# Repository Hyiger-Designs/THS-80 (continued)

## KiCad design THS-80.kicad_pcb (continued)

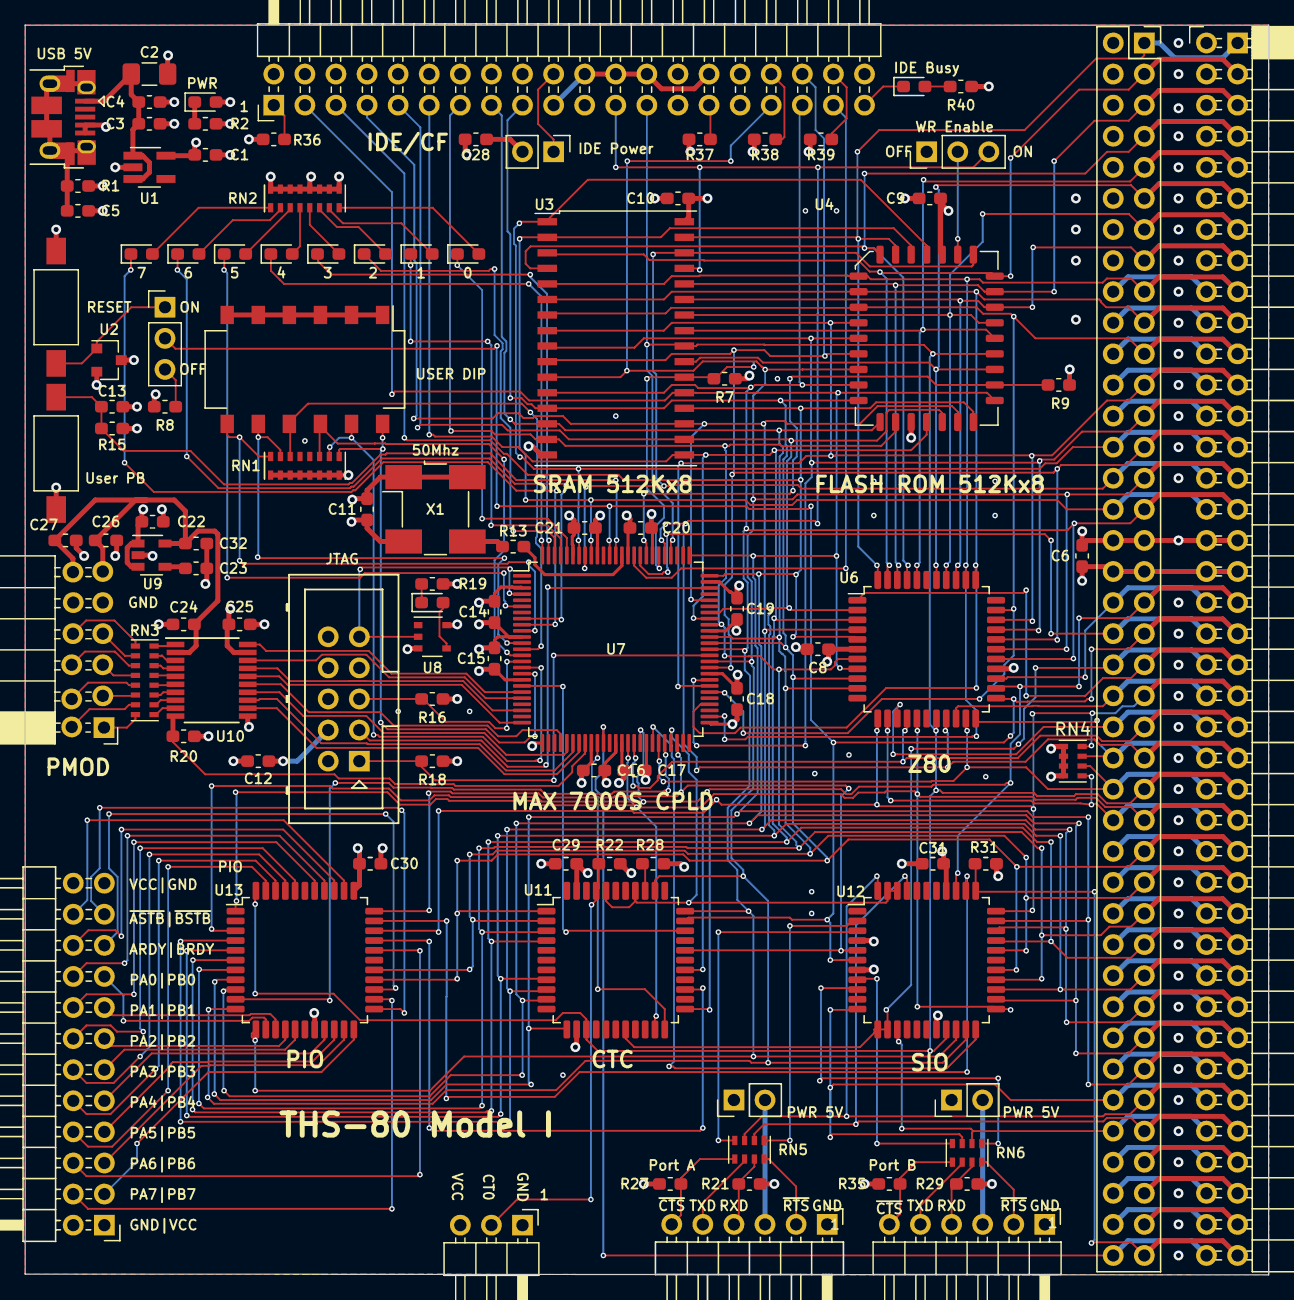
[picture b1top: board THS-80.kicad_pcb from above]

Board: 4 copper layers, 101.6 x 102.1 mm, 102 parts (0 on the bottom side), 188 nets.

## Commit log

2019-08-15 first version
2019-08-15 fixed project library path
2019-08-15 reset annotations, added dip switch
2019-08-15 added switch pullups
2019-08-15 regridded
2019-08-16 connect sheet pins
2019-08-21 connected sheet pins to bus
2019-08-22 Moved CPU, RAM, ROM to sub-sheet
2019-08-22 fixed up interrupt chain wiring
2019-09-02 fixed bus connections
2019-09-03 passed DRC
2019-09-04 started routing
2019-09-05 more routing
2019-09-05 almost there...
2019-09-06 finished routing, passed DRC
2019-09-06 added top/bottom gnd planes and stitching vias
2019-09-06 stitching via tracks added
2019-09-07 pmod changes
2019-09-17 finished routing, drc passed
2019-09-18 track cleanup, fixed slots in ground plane
2019-09-18 more trace cleanup
2019-09-18 fixed gnd plane breaks, adjust silk screens
2019-09-19 more grnd plane fixes
2019-09-19 fixed pmod pins
2019-09-19 tightened routing
2019-09-20 lots of fixes
2019-09-20 fixed led values, added pwr led
2019-09-20 fixes for CTC and additional clocks
2019-09-21 swapped CTC and PIO
2019-09-24 added bypass for jtag
2019-09-25 rerouting
2019-09-25 replaced VCC with 5V, fixed ROM footprint
2019-10-07 routing checkpoint
2019-10-08 layout changes, silkscreen fixes
2019-10-08 more layout changes
2019-10-08 different path
2019-10-08 checkpoint
2019-10-10 changed regulator, routing
2019-10-12 routing
2019-10-18 cleaned up
2019-10-25 trace cleanup
2019-10-29 gnd plane fixes
2019-11-27 Fixes for rom
2020-01-12 fixed up traces and gnd plane
2020-04-09 Added reset and rom write ena jumpers
2020-04-10 Changed to resistor arrays, flipped to front-side
2020-04-10 removed extraneous components
2020-04-10 straightened traces
2020-04-12 trace smoothing, drc fixes
2020-04-17 More trace smoothing
2020-04-18 fixed clocks
2020-10-09 do over with additional pmod
